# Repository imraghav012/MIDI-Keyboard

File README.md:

# MIDI Keyboard
GitHub repo for Half-Life Week 3 starter project. Building a MIDI keyboard.
This repository contains all of the files for the build, including PCB files, Firmware files, BOM.csv, and a journal of my work.

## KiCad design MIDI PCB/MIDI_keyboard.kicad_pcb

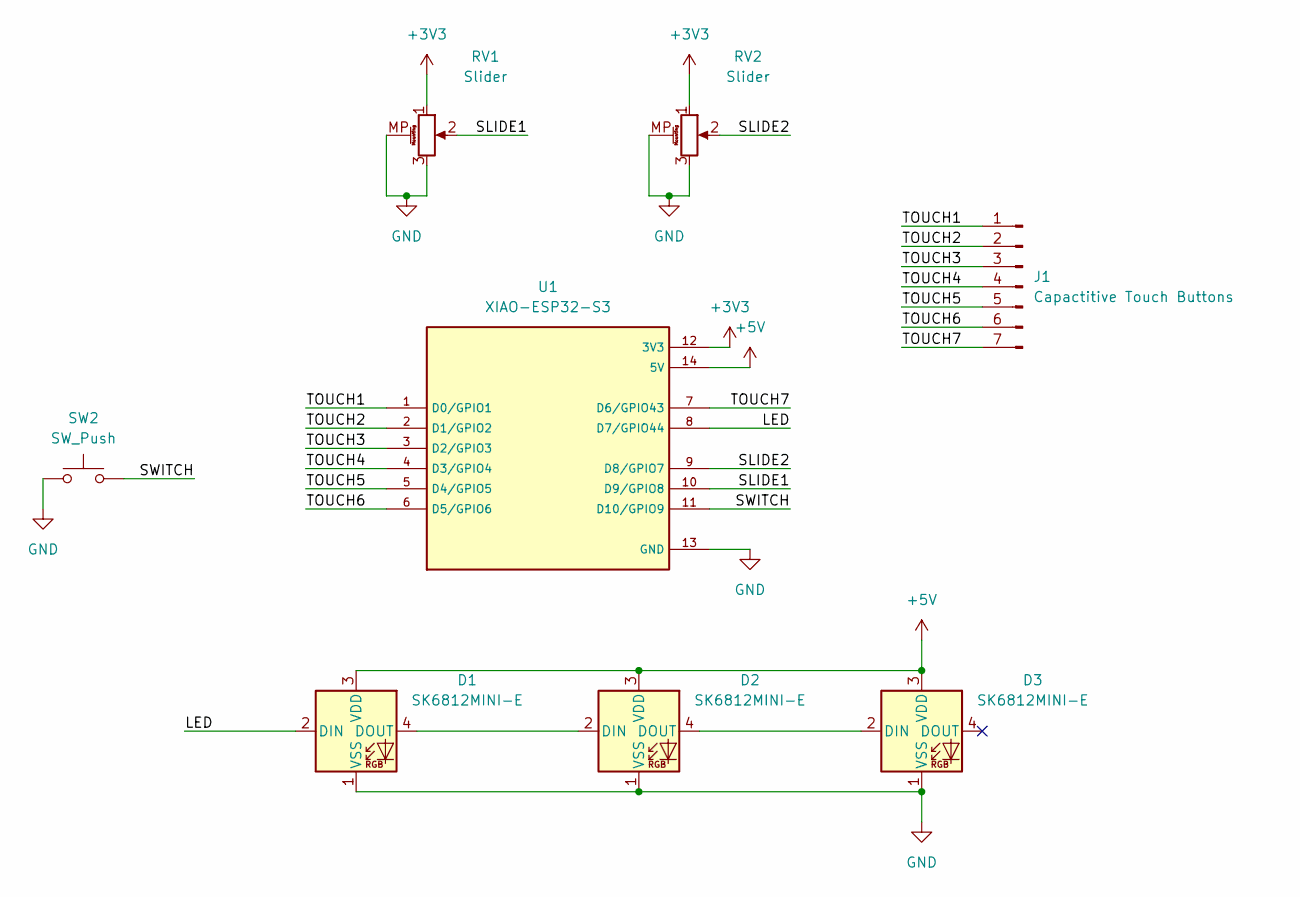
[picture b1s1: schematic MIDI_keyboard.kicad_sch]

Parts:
D1, D2, D3: SK6812MINI-E; LED_SK6812MINI-E_3.2x2.8mm_P1.5mm_ReverseMount
J1: Capactitive Touch Buttons; Capacitive Keys
RV1, RV2: Slider; Potentiometer_Bourns_PTA1543_Single_Slide
SW2: SW_Push; Kailh Choc Low-Profile Switches
U1: XIAO-ESP32-S3; XIAO ESP32-S3; PARTREV April 22nd, 2026

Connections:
+3V3: RV1.1, RV2.1, U1.12 (3V3)
+5V: D1.3 (VDD), D2.3 (VDD), D3.3 (VDD), U1.14 (5V)
/LED: D1.2 (DIN), U1.8 (D7/GPIO44)
/SLIDE1: RV1.2, U1.10 (D9/GPIO8)
/SLIDE2: RV2.2, U1.9 (D8/GPIO7)
/SWITCH: SW2.2, U1.11 (D10/GPIO9)
/TOUCH1: J1.1, U1.1 (D0/GPIO1)
/TOUCH2: J1.2, U1.2 (D1/GPIO2)
/TOUCH3: J1.3, U1.3 (D2/GPIO3)
/TOUCH4: J1.4, U1.4 (D3/GPIO4)
/TOUCH5: J1.5, U1.5 (D4/GPIO5)
/TOUCH6: J1.6, U1.6 (D5/GPIO6)
/TOUCH7: J1.7, U1.7 (D6/GPIO43)
GND: D1.1 (VSS), D2.1 (VSS), D3.1 (VSS), RV1.3, RV1.MP (MountPin), RV2.3, RV2.MP (MountPin), SW2.1, U1.13 (GND)
unnamed: D1.4 (DOUT), D2.2 (DIN)
unnamed: D2.4 (DOUT), D3.2 (DIN)

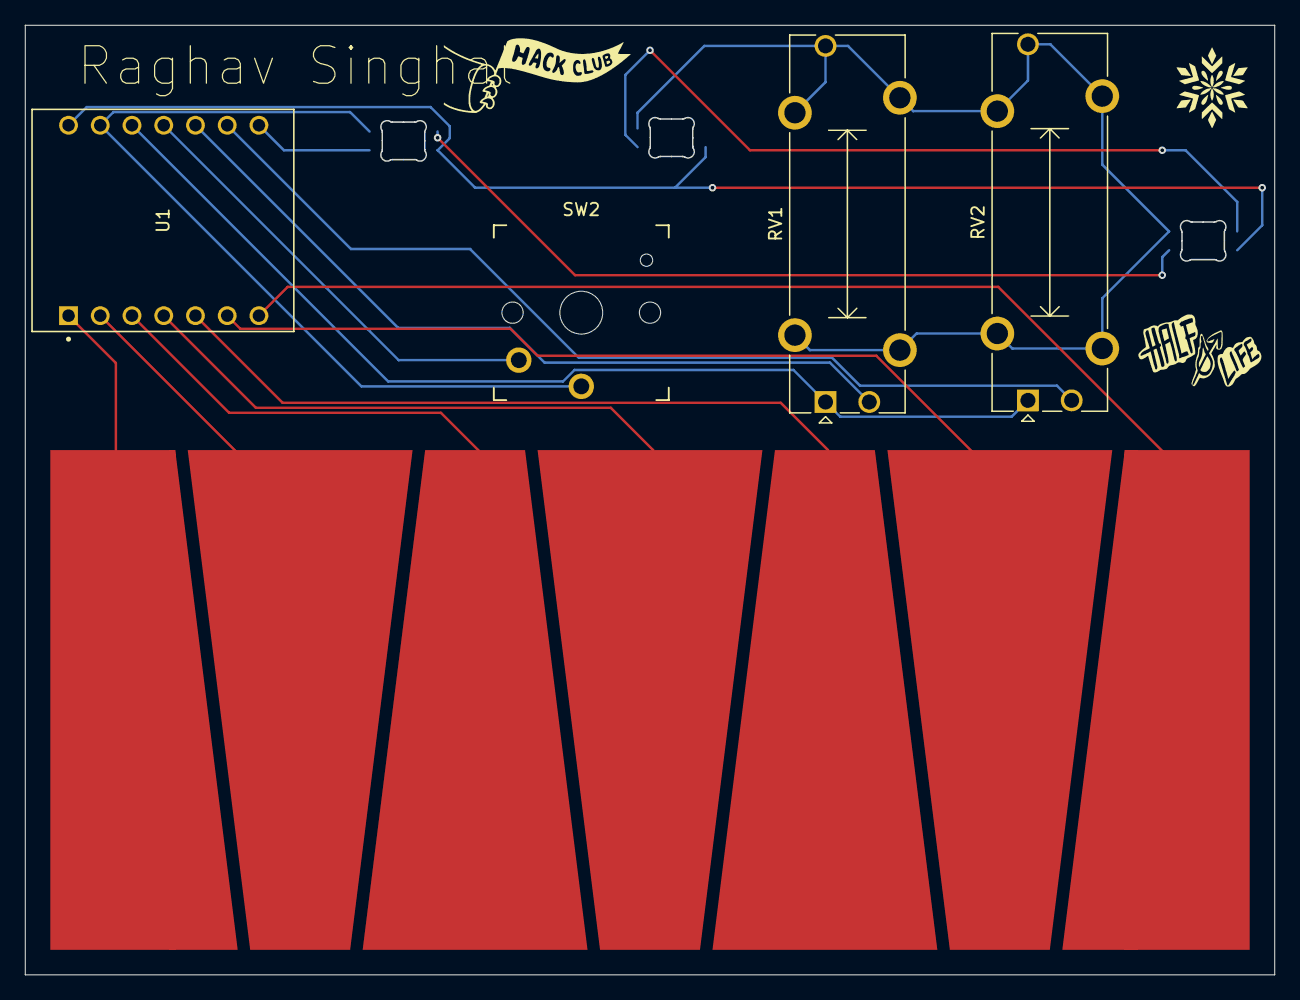
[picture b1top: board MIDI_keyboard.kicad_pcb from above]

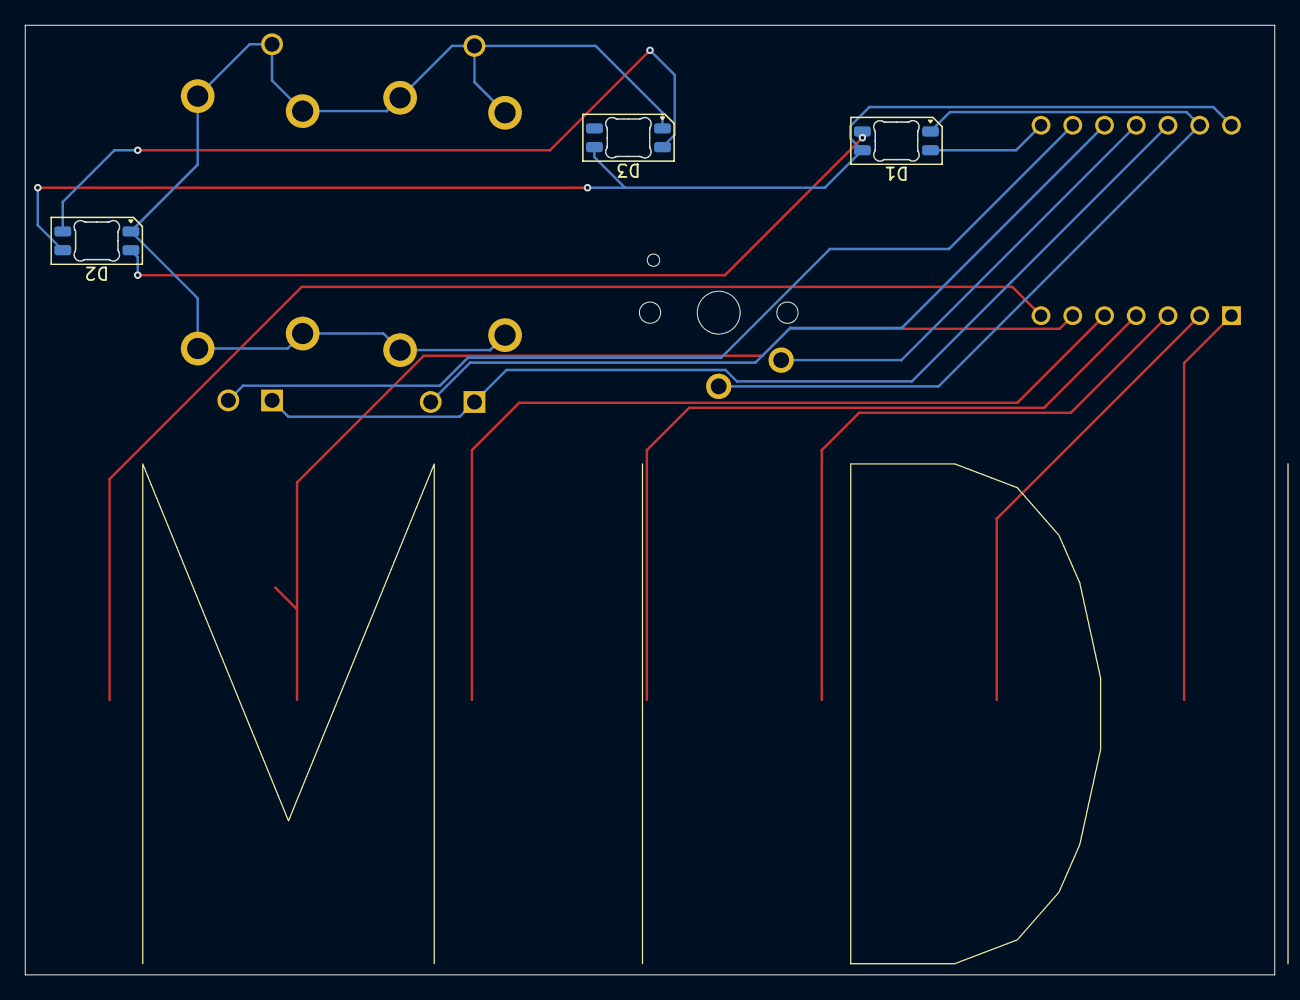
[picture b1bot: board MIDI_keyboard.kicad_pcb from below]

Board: 2 copper layers, 100.0 x 76.0 mm, 8 parts (3 on the bottom side), 16 nets.
